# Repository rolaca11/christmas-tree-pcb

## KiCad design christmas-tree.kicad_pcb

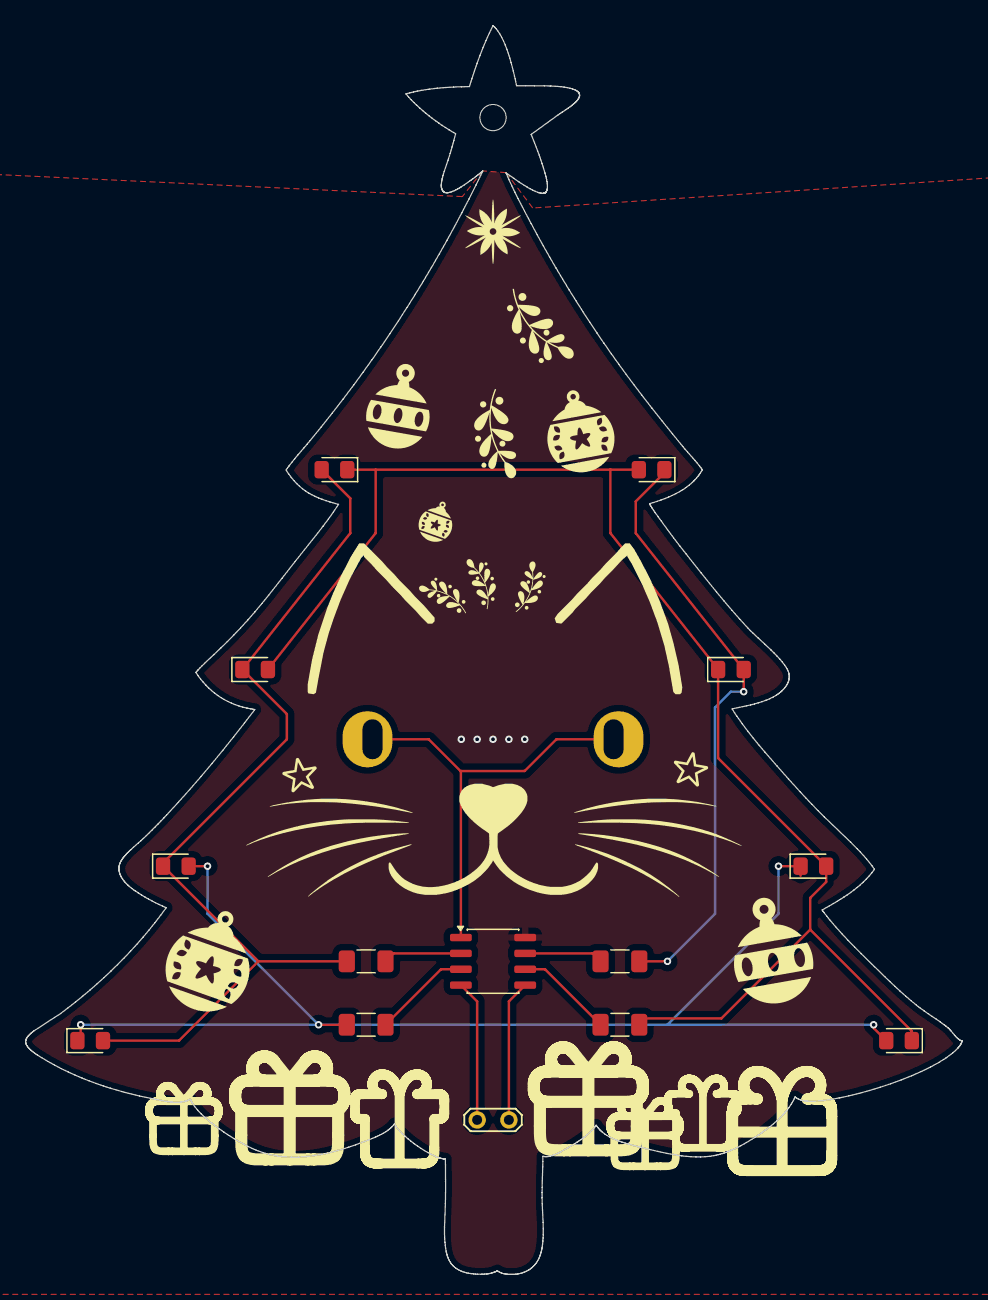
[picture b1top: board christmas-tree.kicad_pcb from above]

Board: 2 copper layers, 75.0 x 100.0 mm, 16 parts (1 on the bottom side), 12 nets.

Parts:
BT1: 9; BatteryHolder_WJ-CR2032-1-W
D1, D2, D3, D4, D5, D6, D7, D8: LED; LED_0805_2012Metric_Pad1.15x1.40mm_HandSolder
H1: MountingHole; MountingHole_2.1mm
R1, R2, R3, R4: 120; R_1206_3216Metric_Pad1.30x1.75mm_HandSolder
TP1: TestPoint_2Pole; TestPoint_2Pads_Pitch2.54mm_Drill0.8mm
U1: PY32F002AL15S6TU; SO-8_3.9x4.9mm_P1.27mm

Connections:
+3V: BT1.1 (+), U1.1 (VCC)
GND: BT1.2 (-), U1.8 (GND)
unnamed: D1.2 (A), D3.1 (K), D5.1 (K), D6.2 (A), R1.1
unnamed: D1.1 (K), D2.2 (A), D3.2 (A), D4.1 (K), R2.1
unnamed: D2.1 (K), D4.2 (A), D5.2 (A), D6.1 (K), D7.2 (A), D8.1 (K), R3.1
unnamed: D7.1 (K), D8.2 (A), R4.1
unnamed: R4.2, U1.7 (PA1)
unnamed: R3.2, U1.6 (PA2)
unnamed: R2.2, U1.3 (PA3)
unnamed: R1.2, U1.2 (PA4)
unnamed: TP1.2, U1.5 (PA13-SWD)
unnamed: TP1.1, U1.4 (PB3/SWCLK)

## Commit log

2025-11-29 JLC Order placed #1
